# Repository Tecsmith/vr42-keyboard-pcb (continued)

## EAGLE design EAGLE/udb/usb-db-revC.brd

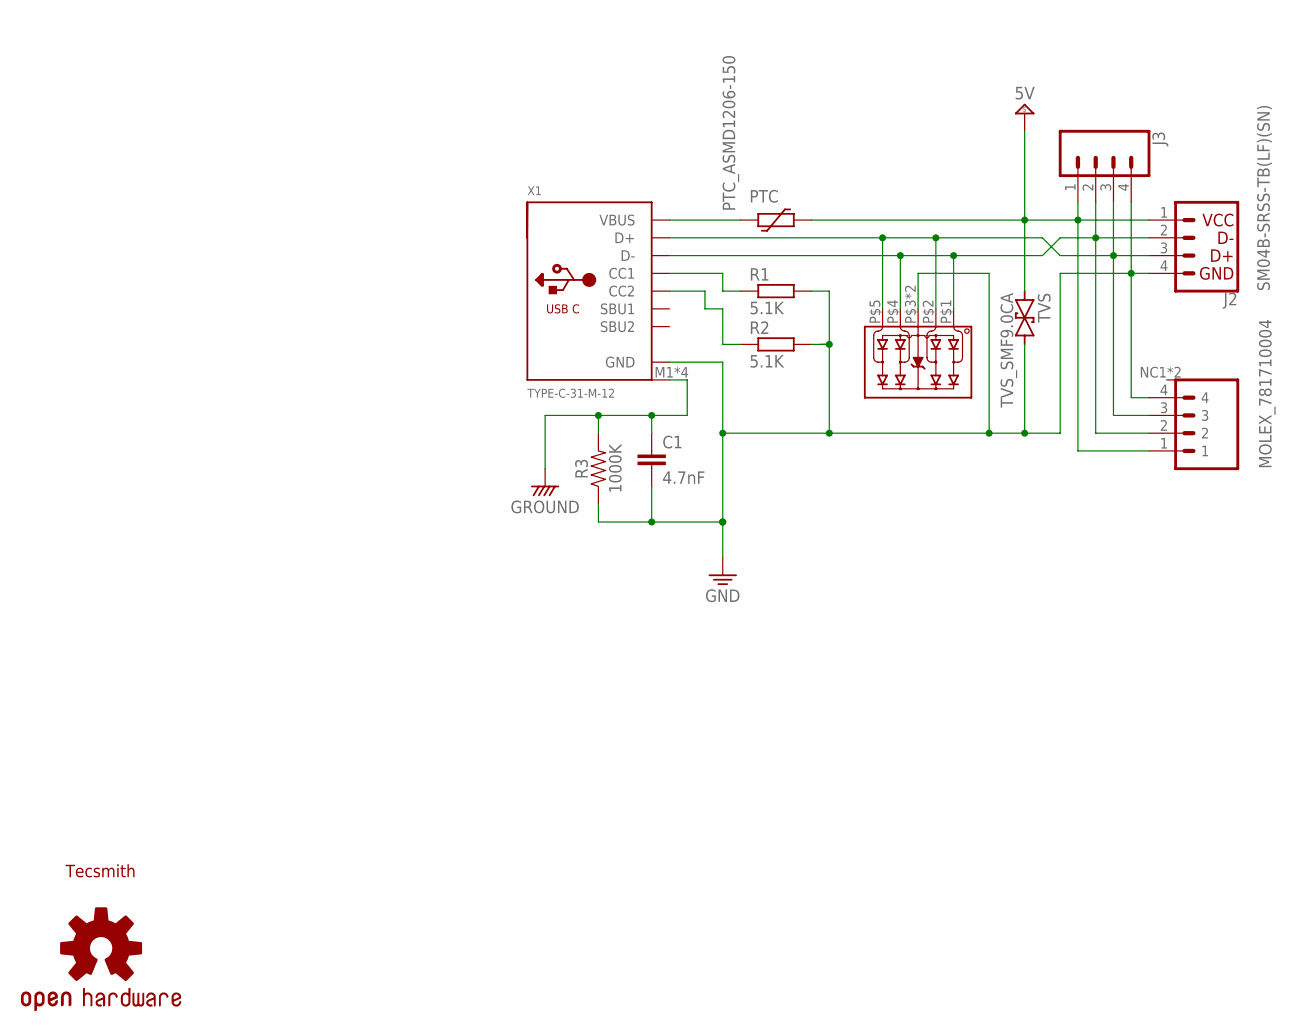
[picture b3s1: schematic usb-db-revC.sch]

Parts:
C1: 4.7nF; 0603
J2: SM04B-SRSS-TB(LF)(SN); 1X04_1MM_RA
J3: CONN_04SMD_RA_FEMALE; 1X04_SMD_RA_FEMALE
LOGO1: OSHW-LOGOS; OSHW-LOGO-S
MOLEX_781710004: MOLEX_0781710004; MOLEX_781710004
PTC: PTC_ASMD1206-150; SMD_PTC
R1, R2: 5.1K; R0402
R3: 1000K; 0603
TVS: TVS_SMF9.0CA; SOD123FL-BI
U$2: TECSMITH-LOGOSHORT; TECSMITH-CUBE
X1: TYPE-C-31-M-12
Y1: ESD_TPD4E05U06; DQA-10-PIN

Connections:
CC1: R1.1, X1.A5-CC1 (CC1)
CC2: R2.1, X1.B5-CC2 (CC2)
D_N: J2.2 (D-), J3.2, MOLEX_781710004.2, X1.A7-DN1 (D-), X1.B7-DN2 (D-), Y1.P$1 (D1+), Y1.P$4 (D2+)
D_P: J2.3 (D+), J3.3, MOLEX_781710004.3, X1.A6-DP1 (D+), X1.B6-DP2 (D+), Y1.P$2 (D1-), Y1.P$5 (D2-)
GND: C1.2, J2.4 (GND), J3.4, MOLEX_781710004.4, R1.2, R2.2, R3.1, TVS.P$2 (2), X1.A1B12-GND (GND), X1.B1A12-GND (GND), Y1.P$3 (GND), Y1.P$8 (GND)
GROUND: C1.1, R3.2, X1.M1 (SHIELD), X1.M2 (SHIELD), X1.M3 (SHIELD), X1.M4 (SHIELD)
VBUS: PTC.P$1 (1), X1.A4B9-VBUS (VBUS), X1.B4A9-VBUS (VBUS)
VSUP: J2.1 (VCC), J3.1, MOLEX_781710004.1, PTC.P$2 (2), TVS.P$1 (1)

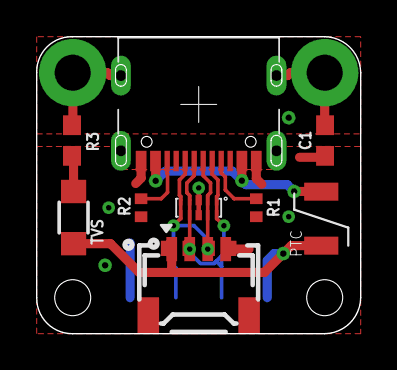
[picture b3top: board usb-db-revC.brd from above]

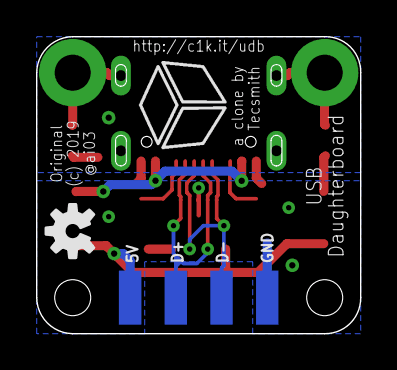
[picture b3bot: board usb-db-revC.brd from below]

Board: 2 copper layers, 18.0 x 16.5 mm, 13 parts (3 on the bottom side), 8 nets.

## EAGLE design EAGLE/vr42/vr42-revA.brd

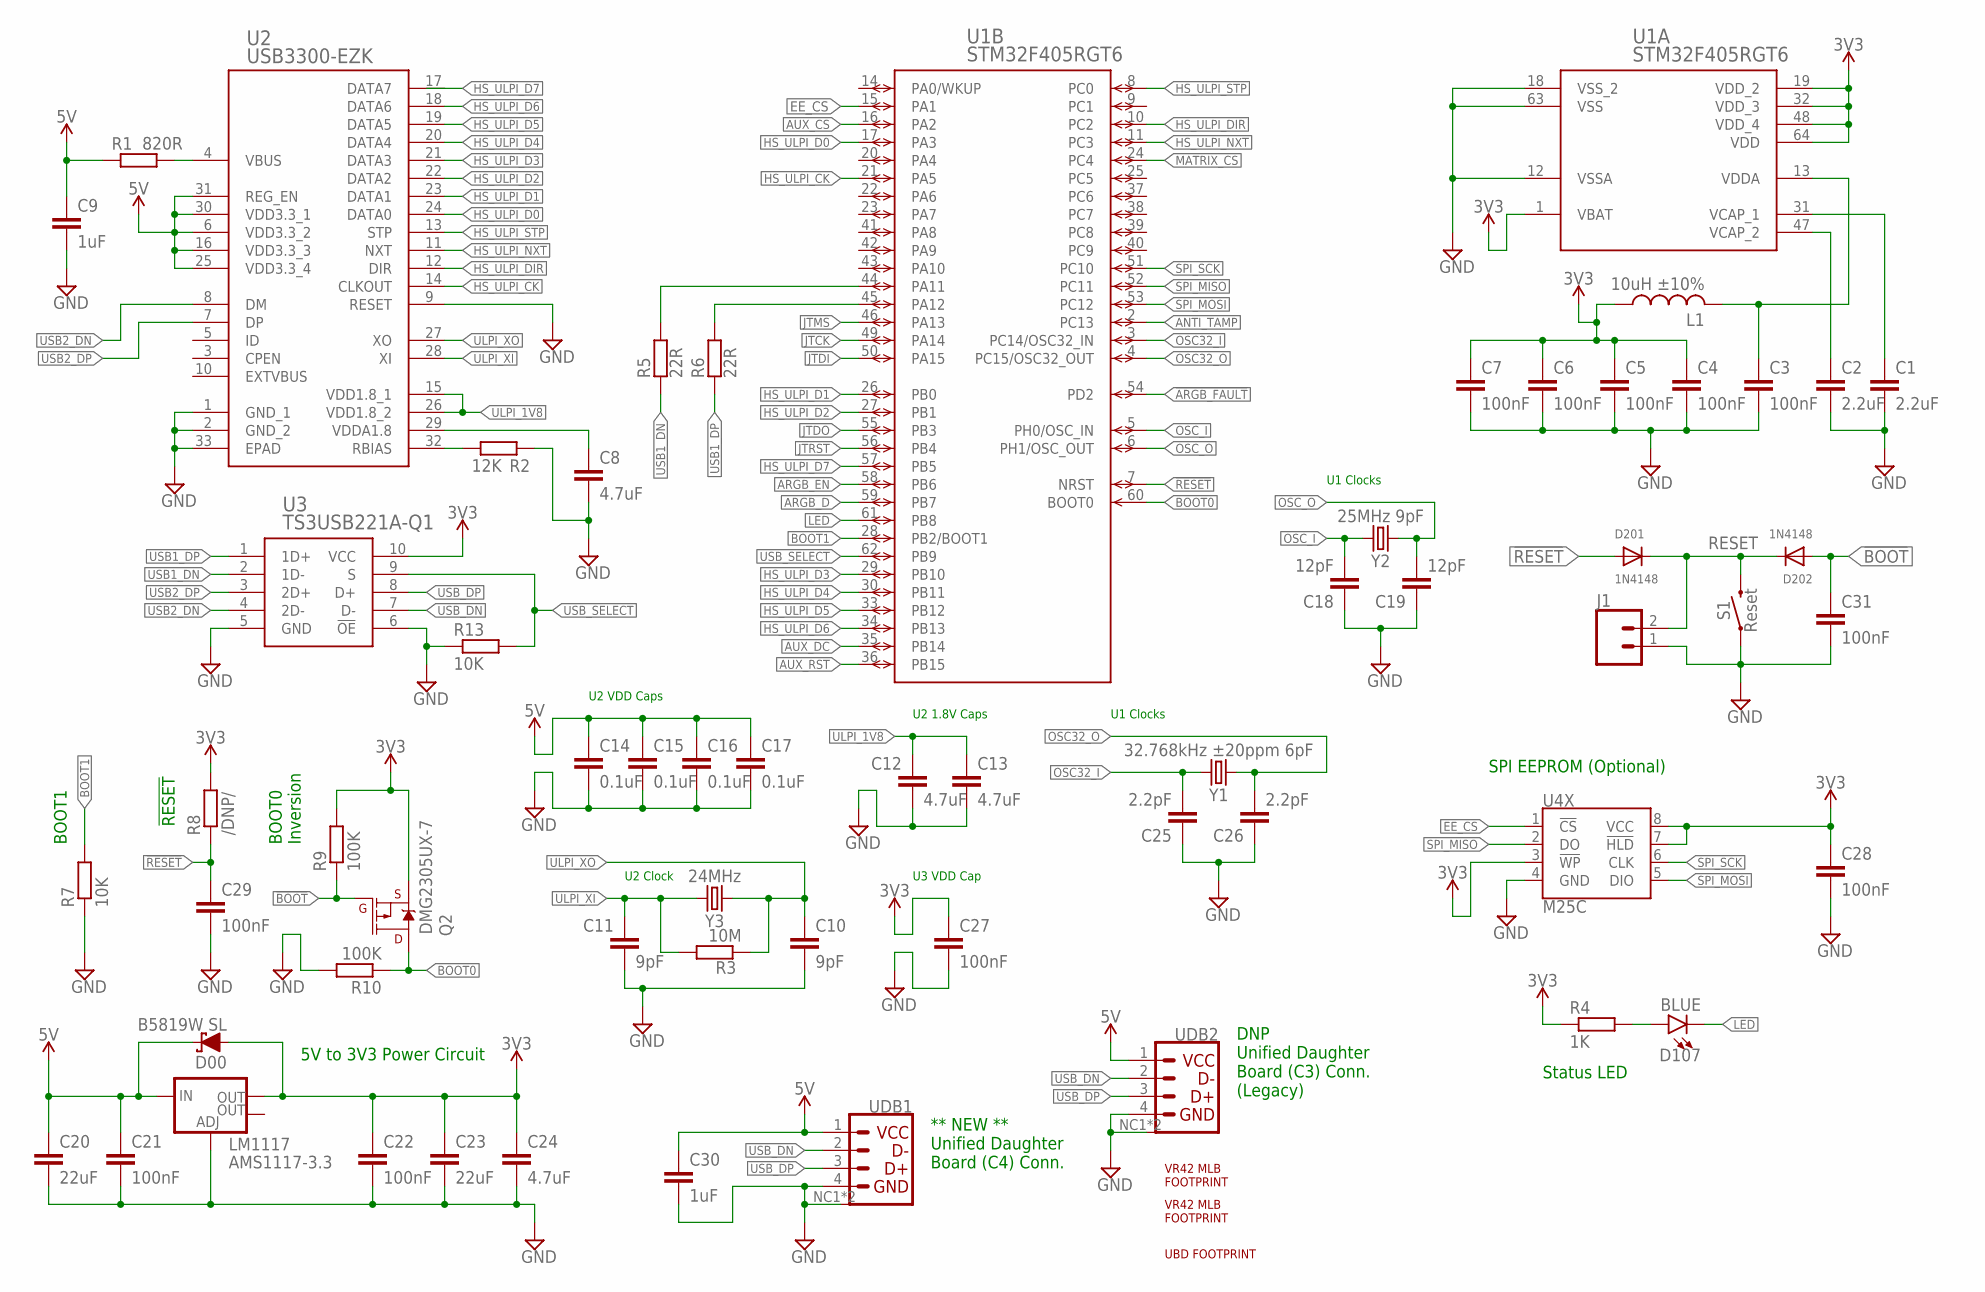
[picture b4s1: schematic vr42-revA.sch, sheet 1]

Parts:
C1, C2: 2.2uF; C0603
C3, C4, C5, C6, C7, C27, C29: 100nF; C0603
C8, C12, C13: 4.7uF; C0603
C9: 1uF; C0603
C10, C11: 9pF; C0603
C14, C15, C16, C17: 0.1uF; C0603
C18, C19: 12pF; C0603
C20, C23: 22uF; 0603
C21, C22, C28: 100nF; 0603
C24: 4.7uF; 0603
C25, C26: 2.2pF; C0603
C30: 1uF; C0805
C31: 100nF; C0805
D00: B5819W SL; SOD-123
D107: BLUE; LED-0603
D201, D202: 1N4148; SOT23-R
J1: CONN_02; 1X02
L1: 10uH ±10%; L3225M
LM1117: AMS1117-3.3; SOT223
Q2: DMG2305UX-7; SOT23-3
R1: 820R; R0603
R2: 12K; R0603
R3: 10M; R0603
R4: 1K; R0603
R5, R6: 22R; R0603
R7, R13: 10K; R0603
R8: /DNP/; R0603
R9, R10: 100K; R0603
S1: Reset; TACTILE_SWITCH_SMD_5.2MM
U1: STM32F405RGT6; LQFP64-10X10MM
U2: USB3300-EZK; QFN32_5X5MC_MCH
U3: TS3USB221A-Q1; RSE10
U4X: M25C; 8-SOIC
U$1, U$6: VR42_MLB_FOOTPRINT
U$7: UBD_FOOTPRINT; UDB_FOOTPRINT
UDB1: UBD-S1_C4; MOLEX_781710004
UDB2: UBD-C3; JST_SM04B-SRSS-TB_LF_SN
Y1: 32.768kHz ±20ppm 6pF; CRYSTAL-SMD-3.2X1.5MM
Y2: 25MHz 9pF; CRYSTAL-SMD-5X3.2-4PAD
Y3: 24MHz; CRYSTAL-SMD-5X3.2-4PAD

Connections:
!ARGB_FAULT: U1.54 (PD2); also elsewhere on the board
!BOOT: C31.1, D202.1 (A), Q2.1 (G), R9.1
!RESET: C29.1, D201.1 (A), R8.1, U1.7 (NRST)
ANTI_TAMP: U1.2 (PC13)
ARGB_D: U1.59 (PB7); also elsewhere on the board
ARGB_EN: U1.58 (PB6); also elsewhere on the board
AUX_CS: U1.16 (PA2); also elsewhere on the board
AUX_DC: U1.35 (PB14); also elsewhere on the board
AUX_RST: U1.36 (PB15); also elsewhere on the board
BOOT0: Q2.3 (D), R10.1, U1.60 (BOOT0)
BOOT1: R7.2, U1.28 (PB2/BOOT1)
EE_CS: U1.15 (PA1), U4X.1 (!CS)
GND: C1.2, C2.2, C3.2, C4.2, C5.2, C6.2, C7.2, C8.2, C9.2, C10.2, C11.2, C12.2, C13.2, C14.2, C15.2, C16.2, C17.2, C18.1, C19.1, C20.2, C21.2, C22.2, C23.2, C24.2, C25.1, C26.1, C27.2, C28.2, C29.2, C30.2, C31.2, J1.1, LM1117.1 (ADJ), R2.2, R7.1, R10.2, R13.1, S1.1, S1.2 (1), U1.12 (VSSA), U1.18 (VSS_2), U1.63 (VSS), U2.1 (GND_1), U2.2 (GND_2), U2.9 (RESET), U2.33 (EPAD), U3.5 (GND), U3.6 (!OE), U4X.4 (GND), UDB1.4 (GND), UDB1.NC1 (M), UDB1.NC2 (M), UDB2.4 (GND), UDB2.NC1 (M), UDB2.NC2 (M); also elsewhere on the board
HS_ULPI_CK: U1.21 (PA5), U2.14 (CLKOUT)
HS_ULPI_D0: U1.17 (PA3), U2.24 (DATA0)
HS_ULPI_D1: U1.26 (PB0), U2.23 (DATA1)
HS_ULPI_D2: U1.27 (PB1), U2.22 (DATA2)
HS_ULPI_D3: U1.29 (PB10), U2.21 (DATA3)
HS_ULPI_D4: U1.30 (PB11), U2.20 (DATA4)
HS_ULPI_D5: U1.33 (PB12), U2.19 (DATA5)
HS_ULPI_D6: U1.34 (PB13), U2.18 (DATA6)
HS_ULPI_D7: U1.57 (PB5), U2.17 (DATA7)
HS_ULPI_DIR: U1.10 (PC2), U2.12 (DIR)
HS_ULPI_NXT: U1.11 (PC3), U2.11 (NXT)
HS_ULPI_STP: U1.8 (PC0), U2.13 (STP)
JTCK: U1.49 (PA14); also elsewhere on the board
JTDI: U1.50 (PA15); also elsewhere on the board
JTDO: U1.55 (PB3); also elsewhere on the board
JTMS: U1.46 (PA13); also elsewhere on the board
JTRST: U1.56 (PB4); also elsewhere on the board
LED: D107.C, U1.61 (PB8)
MATRIX_CS: U1.24 (PC4); also elsewhere on the board
unnamed: R1.2, U2.4 (VBUS)
unnamed: R2.1, U2.32 (RBIAS)
unnamed: C8.1, U2.29 (VDDA1.8)
unnamed: R5.2, U1.44 (PA11)
unnamed: R6.2, U1.45 (PA12)
unnamed: D107.A, R4.2
OSC32_I: C25.2, U1.3 (PC14/OSC32_IN), Y1.P$2 (2)
OSC32_O: C26.2, U1.4 (PC15/OSC32_OUT), Y1.P$1 (1)
OSC_I: C18.2, U1.5 (PH0/OSC_IN), Y2.3 (2)
OSC_O: C19.2, U1.6 (PH1/OSC_OUT), Y2.1
RESET: D201.3 (C), D202.3 (C), J1.2, S1.3 (2), S1.4 (2)
SPI_MISO: U1.52 (PC11), U4X.2 (DO); also elsewhere on the board
SPI_MOSI: U1.53 (PC12), U4X.5 (DIO); also elsewhere on the board
SPI_SCK: U1.51 (PC10), U4X.6 (CLK); also elsewhere on the board
ULPI_1V8: C12.1, C13.1, U2.15 (VDD1.8_1), U2.26 (VDD1.8_2)
ULPI_XI: C11.1, R3.2, U2.28 (XI), Y3.3 (2)
ULPI_XO: C10.1, R3.1, U2.27 (XO), Y3.1
USB1_DN: R5.1, U3.2 (1D-)
USB1_DP: R6.1, U3.1 (1D+)
USB2_DN: U2.8 (DM), U3.4 (2D-)
USB2_DP: U2.7 (DP), U3.3 (2D+)
USB_DN: U3.7 (D-), UDB1.2 (DN), UDB2.2 (DN)
USB_DP: U3.8 (D+), UDB1.3 (DP), UDB2.3 (DP)
USB_SELECT: R13.2, U1.62 (PB9), U3.9 (S)
VCAP_1: C1.1, U1.31 (VCAP_1)
VCAP_2: C2.1, U1.47 (VCAP_2)
VCC_1: C9.1, C14.1, C15.1, C16.1, C17.1, C20.1, C21.1, C30.1, D00.C, LM1117.3 (IN), R1.1, U2.6 (VDD3.3_2), U2.16 (VDD3.3_3), U2.25 (VDD3.3_4), U2.30 (VDD3.3_1), U2.31 (REG_EN), UDB1.1 (VCC), UDB2.1 (VCC); also elsewhere on the board
VCC_2: C4.1, C5.1, C6.1, C7.1, C22.1, C23.1, C24.1, C27.1, C28.1, D00.A, L1.1, LM1117.2 (OUT), Q2.2 (S), R4.1, R8.2, R9.2, U1.1 (VBAT), U1.19 (VDD_2), U1.32 (VDD_3), U1.48 (VDD_4), U1.64 (VDD), U3.10 (VCC), U4X.3 (!WP), U4X.7 (!HLD), U4X.8 (VCC); also elsewhere on the board
VDDA: C3.1, L1.2, U1.13 (VDDA)

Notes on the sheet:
DNP Unified Daughter Board (C3) Conn. (Legacy)
** NEW ** Unified Daughter Board (C4) Conn.
5V to 3V3 Power Circuit
SPI EEPROM (Optional)
BOOT1
BOOT0 Inversion
!RESET
Status LED
U2 VDD Caps
U2 Clock
U3 VDD Cap
U2 1.8V Caps
U1 Clocks

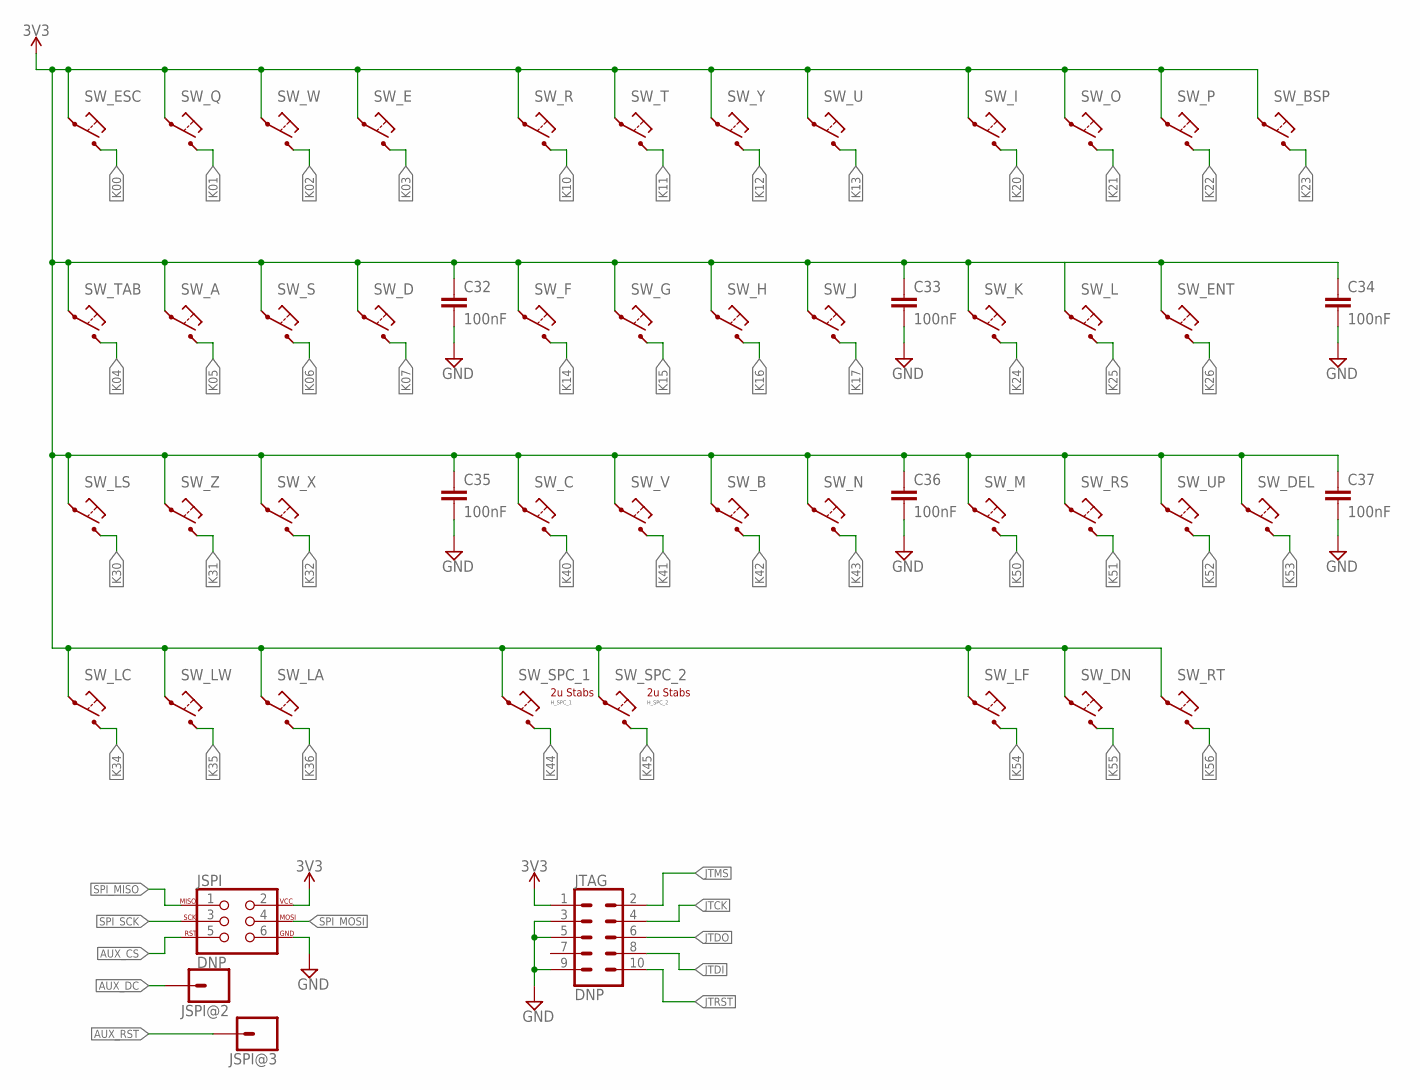
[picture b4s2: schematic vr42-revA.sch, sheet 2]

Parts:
C32, C33, C34, C35, C36, C37: 100nF; C0603
H_SPC_1, H_SPC_2: MX-STABS-200U
JSPI: DNP; 2X3-NS
JSPI@2, JSPI@3: CONN_01; 1X01
JTAG: DNP; 2X5_NOSILK
SW_A: MX-5-PIN-HOTSWAP-PAD
SW_B: MX-5-PIN-HOTSWAP-PAD
SW_BSP: MX-5-PIN-HOTSWAP-PAD
SW_C: MX-5-PIN-HOTSWAP-PAD
SW_D: MX-5-PIN-HOTSWAP-PAD
SW_DEL: MX-5-PIN-HOTSWAP-PAD
SW_DN: MX-5-PIN-HOTSWAP-PAD
SW_E: MX-5-PIN-HOTSWAP-PAD
SW_ENT: MX-5-PIN-HOTSWAP-PAD
SW_ESC: MX-5-PIN-HOTSWAP-PAD
SW_F: MX-5-PIN-HOTSWAP-PAD
SW_G: MX-5-PIN-HOTSWAP-PAD
SW_H: MX-5-PIN-HOTSWAP-PAD
SW_I: MX-5-PIN-HOTSWAP-PAD
SW_J: MX-5-PIN-HOTSWAP-PAD
SW_K: MX-5-PIN-HOTSWAP-PAD
SW_L: MX-5-PIN-HOTSWAP-PAD
SW_LA: MX-5-PIN-HOTSWAP-PAD
SW_LC: MX-5-PIN-HOTSWAP-PAD
SW_LF: MX-5-PIN-HOTSWAP-PAD
SW_LS: MX-5-PIN-HOTSWAP-PAD
SW_LW: MX-5-PIN-HOTSWAP-PAD
SW_M: MX-5-PIN-HOTSWAP-PAD
SW_N: MX-5-PIN-HOTSWAP-PAD
SW_O: MX-5-PIN-HOTSWAP-PAD
SW_P: MX-5-PIN-HOTSWAP-PAD
SW_Q: MX-5-PIN-HOTSWAP-PAD
SW_R: MX-5-PIN-HOTSWAP-PAD
SW_RS: MX-5-PIN-HOTSWAP-PAD
SW_RT: MX-5-PIN-HOTSWAP-PAD
SW_S: MX-5-PIN-HOTSWAP-PAD
SW_SPC_1, SW_SPC_2: MX-5-PIN-HOTSWAP-PAD
SW_T: MX-5-PIN-HOTSWAP-PAD
SW_TAB: MX-5-PIN-HOTSWAP-PAD
SW_U: MX-5-PIN-HOTSWAP-PAD
SW_UP: MX-5-PIN-HOTSWAP-PAD
SW_V: MX-5-PIN-HOTSWAP-PAD
SW_W: MX-5-PIN-HOTSWAP-PAD
SW_X: MX-5-PIN-HOTSWAP-PAD
SW_Y: MX-5-PIN-HOTSWAP-PAD
SW_Z: MX-5-PIN-HOTSWAP-PAD

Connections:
AUX_CS: JSPI.5; also elsewhere on the board
AUX_DC: JSPI@2.1; also elsewhere on the board
AUX_RST: JSPI@3.1; also elsewhere on the board
GND: C32.2, C33.2, C34.2, C35.2, C36.2, C37.2, JSPI.6, JTAG.3, JTAG.5, JTAG.9; also elsewhere on the board
JTCK: JTAG.4; also elsewhere on the board
JTDI: JTAG.8; also elsewhere on the board
JTDO: JTAG.6; also elsewhere on the board
JTMS: JTAG.2; also elsewhere on the board
JTRST: JTAG.10; also elsewhere on the board
K00: SW_ESC.1@1, SW_ESC.1@2; also elsewhere on the board
K01: SW_Q.1@1, SW_Q.1@2; also elsewhere on the board
K02: SW_W.1@1, SW_W.1@2; also elsewhere on the board
K03: SW_E.1@1, SW_E.1@2; also elsewhere on the board
K04: SW_TAB.1@1, SW_TAB.1@2; also elsewhere on the board
K05: SW_A.1@1, SW_A.1@2; also elsewhere on the board
K06: SW_S.1@1, SW_S.1@2; also elsewhere on the board
K07: SW_D.1@1, SW_D.1@2; also elsewhere on the board
K10: SW_R.1@1, SW_R.1@2; also elsewhere on the board
K11: SW_T.1@1, SW_T.1@2; also elsewhere on the board
K12: SW_Y.1@1, SW_Y.1@2; also elsewhere on the board
K13: SW_U.1@1, SW_U.1@2; also elsewhere on the board
K14: SW_F.1@1, SW_F.1@2; also elsewhere on the board
K15: SW_G.1@1, SW_G.1@2; also elsewhere on the board
K16: SW_H.1@1, SW_H.1@2; also elsewhere on the board
K17: SW_J.1@1, SW_J.1@2; also elsewhere on the board
K20: SW_I.1@1, SW_I.1@2; also elsewhere on the board
K21: SW_O.1@1, SW_O.1@2; also elsewhere on the board
K22: SW_P.1@1, SW_P.1@2; also elsewhere on the board
K23: SW_BSP.1@1, SW_BSP.1@2; also elsewhere on the board
K24: SW_K.1@1, SW_K.1@2; also elsewhere on the board
K25: SW_L.1@1, SW_L.1@2; also elsewhere on the board
K26: SW_ENT.1@1, SW_ENT.1@2; also elsewhere on the board
K30: SW_LS.1@1, SW_LS.1@2; also elsewhere on the board
K31: SW_Z.1@1, SW_Z.1@2; also elsewhere on the board
K32: SW_X.1@1, SW_X.1@2; also elsewhere on the board
K34: SW_LC.1@1, SW_LC.1@2; also elsewhere on the board
K35: SW_LW.1@1, SW_LW.1@2; also elsewhere on the board
K36: SW_LA.1@1, SW_LA.1@2; also elsewhere on the board
K40: SW_C.1@1, SW_C.1@2; also elsewhere on the board
K41: SW_V.1@1, SW_V.1@2; also elsewhere on the board
K42: SW_B.1@1, SW_B.1@2; also elsewhere on the board
K43: SW_N.1@1, SW_N.1@2; also elsewhere on the board
K44: SW_SPC_1.1@1, SW_SPC_1.1@2; also elsewhere on the board
K45: SW_SPC_2.1@1, SW_SPC_2.1@2; also elsewhere on the board
K50: SW_M.1@1, SW_M.1@2; also elsewhere on the board
K51: SW_RS.1@1, SW_RS.1@2; also elsewhere on the board
K52: SW_UP.1@1, SW_UP.1@2; also elsewhere on the board
K53: SW_DEL.1@1, SW_DEL.1@2; also elsewhere on the board
K54: SW_LF.1@1, SW_LF.1@2; also elsewhere on the board
K55: SW_DN.1@1, SW_DN.1@2; also elsewhere on the board
K56: SW_RT.1@1, SW_RT.1@2; also elsewhere on the board
SPI_MISO: JSPI.1; also elsewhere on the board
SPI_MOSI: JSPI.4; also elsewhere on the board
SPI_SCK: JSPI.3; also elsewhere on the board
VCC_2: C32.1, C33.1, C34.1, C35.1, C36.1, C37.1, JSPI.2, JTAG.1, SW_A.2@1 (S), SW_A.2@2 (S), SW_B.2@1 (S), SW_B.2@2 (S), SW_BSP.2@1 (S), SW_BSP.2@2 (S), SW_C.2@1 (S), SW_C.2@2 (S), SW_D.2@1 (S), SW_D.2@2 (S), SW_DEL.2@1 (S), SW_DEL.2@2 (S), SW_DN.2@1 (S), SW_DN.2@2 (S), SW_E.2@1 (S), SW_E.2@2 (S), SW_ENT.2@1 (S), SW_ENT.2@2 (S), SW_ESC.2@1 (S), SW_ESC.2@2 (S), SW_F.2@1 (S), SW_F.2@2 (S), SW_G.2@1 (S), SW_G.2@2 (S), SW_H.2@1 (S), SW_H.2@2 (S), SW_I.2@1 (S), SW_I.2@2 (S), SW_J.2@1 (S), SW_J.2@2 (S), SW_K.2@1 (S), SW_K.2@2 (S), SW_L.2@1 (S), SW_L.2@2 (S), SW_LA.2@1 (S), SW_LA.2@2 (S), SW_LC.2@1 (S), SW_LC.2@2 (S), SW_LF.2@1 (S), SW_LF.2@2 (S), SW_LS.2@1 (S), SW_LS.2@2 (S), SW_LW.2@1 (S), SW_LW.2@2 (S), SW_M.2@1 (S), SW_M.2@2 (S), SW_N.2@1 (S), SW_N.2@2 (S), SW_O.2@1 (S), SW_O.2@2 (S), SW_P.2@1 (S), SW_P.2@2 (S), SW_Q.2@1 (S), SW_Q.2@2 (S), SW_R.2@1 (S), SW_R.2@2 (S), SW_RS.2@1 (S), SW_RS.2@2 (S), SW_RT.2@1 (S), SW_RT.2@2 (S), SW_S.2@1 (S), SW_S.2@2 (S), SW_SPC_1.2@1 (S), SW_SPC_1.2@2 (S), SW_SPC_2.2@1 (S), SW_SPC_2.2@2 (S), SW_T.2@1 (S), SW_T.2@2 (S), SW_TAB.2@1 (S), SW_TAB.2@2 (S), SW_U.2@1 (S), SW_U.2@2 (S), SW_UP.2@1 (S), SW_UP.2@2 (S), SW_V.2@1 (S), SW_V.2@2 (S), SW_W.2@1 (S), SW_W.2@2 (S), SW_X.2@1 (S), SW_X.2@2 (S), SW_Y.2@1 (S), SW_Y.2@2 (S), SW_Z.2@1 (S), SW_Z.2@2 (S); also elsewhere on the board

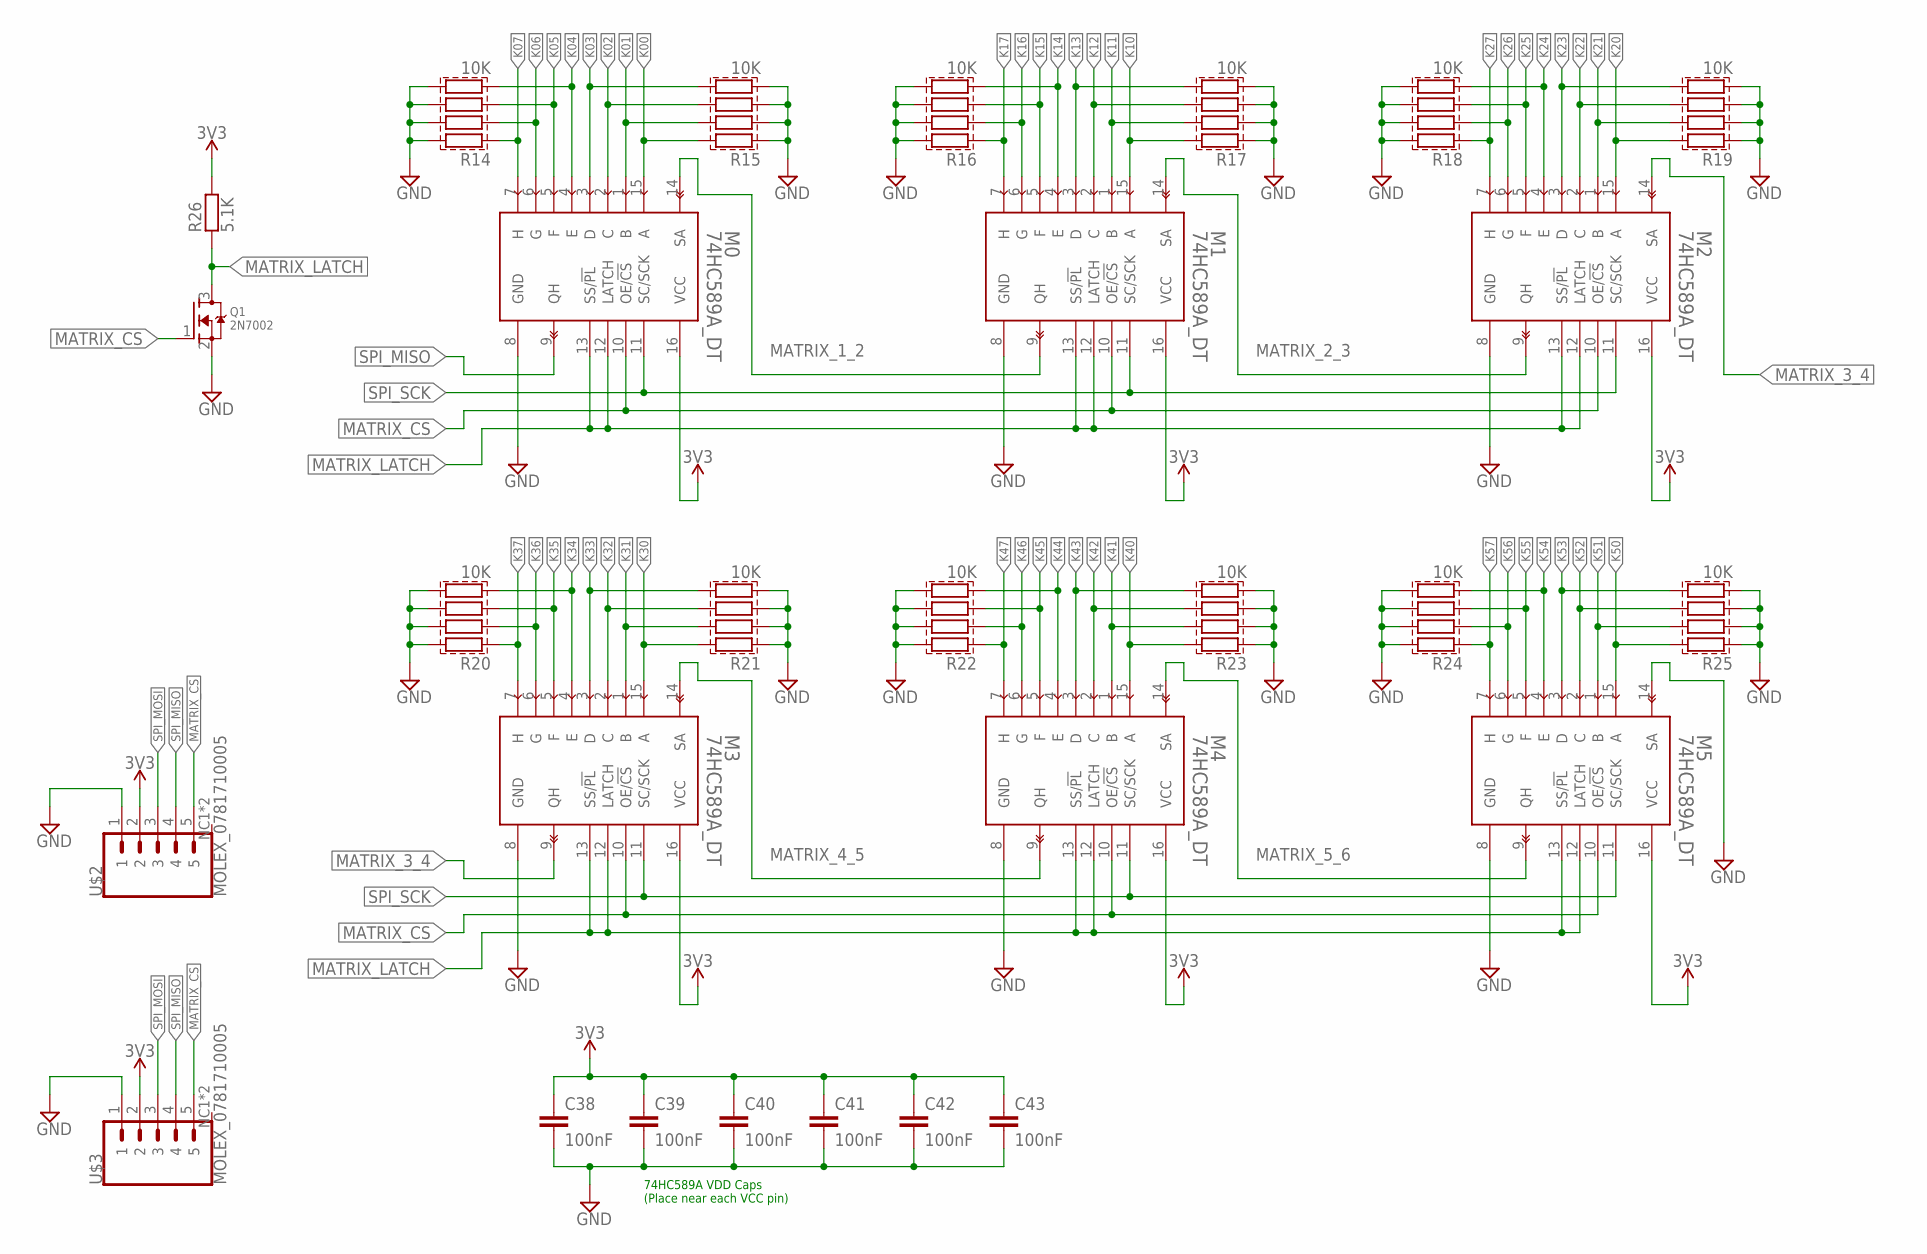
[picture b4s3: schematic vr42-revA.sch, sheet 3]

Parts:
C38, C39, C40, C41, C42, C43: 100nF; 0603
M0, M1, M2, M3, M4, M5: 74HC589A_DT; TSSOP16
Q1: 2N7002; SOT23
R14, R15, R16, R17, R18, R19, R20, R21, R22, R23, R24, R25: 10K; R0603X4
R26: 5.1K; R0603
U$2, U$3: MOLEX_0781710005; MOLEX_781710005

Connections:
GND: C38.2, C39.2, C40.2, C41.2, C42.2, C43.2, M0.8 (GND), M1.8 (GND), M2.8 (GND), M3.8 (GND), M4.8 (GND), M5.8 (GND), M5.14 (SA), Q1.2 (S), R14.5, R14.6, R14.7, R14.8, R15.1, R15.2, R15.3, R15.4, R16.5, R16.6, R16.7, R16.8, R17.1, R17.2, R17.3, R17.4, R18.5, R18.6, R18.7, R18.8, R19.1, R19.2, R19.3, R19.4, R20.5, R20.6, R20.7, R20.8, R21.1, R21.2, R21.3, R21.4, R22.5, R22.6, R22.7, R22.8, R23.1, R23.2, R23.3, R23.4, R24.5, R24.6, R24.7, R24.8, R25.1, R25.2, R25.3, R25.4, U$2.1, U$3.1; also elsewhere on the board
K00: M0.15 (A), R15.8; also elsewhere on the board
K01: M0.1 (B), R15.7; also elsewhere on the board
K02: M0.2 (C), R15.6; also elsewhere on the board
K03: M0.3 (D), R15.5; also elsewhere on the board
K04: M0.4 (E), R14.4; also elsewhere on the board
K05: M0.5 (F), R14.3; also elsewhere on the board
K06: M0.6 (G), R14.2; also elsewhere on the board
K07: M0.7 (H), R14.1; also elsewhere on the board
K10: M1.15 (A), R17.8; also elsewhere on the board
K11: M1.1 (B), R17.7; also elsewhere on the board
K12: M1.2 (C), R17.6; also elsewhere on the board
K13: M1.3 (D), R17.5; also elsewhere on the board
K14: M1.4 (E), R16.4; also elsewhere on the board
K15: M1.5 (F), R16.3; also elsewhere on the board
K16: M1.6 (G), R16.2; also elsewhere on the board
K17: M1.7 (H), R16.1; also elsewhere on the board
K20: M2.15 (A), R19.8; also elsewhere on the board
K21: M2.1 (B), R19.7; also elsewhere on the board
K22: M2.2 (C), R19.6; also elsewhere on the board
K23: M2.3 (D), R19.5; also elsewhere on the board
K24: M2.4 (E), R18.4; also elsewhere on the board
K25: M2.5 (F), R18.3; also elsewhere on the board
K26: M2.6 (G), R18.2; also elsewhere on the board
K27: M2.7 (H), R18.1
K30: M3.15 (A), R21.8; also elsewhere on the board
K31: M3.1 (B), R21.7; also elsewhere on the board
K32: M3.2 (C), R21.6; also elsewhere on the board
K33: M3.3 (D), R21.5
K34: M3.4 (E), R20.4; also elsewhere on the board
K35: M3.5 (F), R20.3; also elsewhere on the board
K36: M3.6 (G), R20.2; also elsewhere on the board
K37: M3.7 (H), R20.1
K40: M4.15 (A), R23.8; also elsewhere on the board
K41: M4.1 (B), R23.7; also elsewhere on the board
K42: M4.2 (C), R23.6; also elsewhere on the board
K43: M4.3 (D), R23.5; also elsewhere on the board
K44: M4.4 (E), R22.4; also elsewhere on the board
K45: M4.5 (F), R22.3; also elsewhere on the board
K46: M4.6 (G), R22.2
K47: M4.7 (H), R22.1
K50: M5.15 (A), R25.8; also elsewhere on the board
K51: M5.1 (B), R25.7; also elsewhere on the board
K52: M5.2 (C), R25.6; also elsewhere on the board
K53: M5.3 (D), R25.5; also elsewhere on the board
K54: M5.4 (E), R24.4; also elsewhere on the board
K55: M5.5 (F), R24.3; also elsewhere on the board
K56: M5.6 (G), R24.2; also elsewhere on the board
K57: M5.7 (H), R24.1
MATRIX_1_2: M0.14 (SA), M1.9 (QH)
MATRIX_2_3: M1.14 (SA), M2.9 (QH)
MATRIX_3_4: M2.14 (SA), M3.9 (QH)
MATRIX_4_5: M3.14 (SA), M4.9 (QH)
MATRIX_5_6: M4.14 (SA), M5.9 (QH)
MATRIX_CS: M0.10 (OE/!CS), M1.10 (OE/!CS), M2.10 (OE/!CS), M3.10 (OE/!CS), M4.10 (OE/!CS), M5.10 (OE/!CS), Q1.1 (G), U$2.5, U$3.5; also elsewhere on the board
MATRIX_LATCH: M0.12 (LATCH), M0.13 (SS/!PL), M1.12 (LATCH), M1.13 (SS/!PL), M2.12 (LATCH), M2.13 (SS/!PL), M3.12 (LATCH), M3.13 (SS/!PL), M4.12 (LATCH), M4.13 (SS/!PL), M5.12 (LATCH), M5.13 (SS/!PL), Q1.3 (D), R26.1
SPI_MISO: M0.9 (QH), U$2.4, U$3.4; also elsewhere on the board
SPI_MOSI: U$2.3, U$3.3; also elsewhere on the board
SPI_SCK: M0.11 (SC/SCK), M1.11 (SC/SCK), M2.11 (SC/SCK), M3.11 (SC/SCK), M4.11 (SC/SCK), M5.11 (SC/SCK); also elsewhere on the board
VCC_2: C38.1, C39.1, C40.1, C41.1, C42.1, C43.1, M0.16 (VCC), M1.16 (VCC), M2.16 (VCC), M3.16 (VCC), M4.16 (VCC), M5.16 (VCC), R26.2, U$2.2, U$3.2; also elsewhere on the board

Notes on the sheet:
74HC589A VDD Caps (Place near each VCC pin)

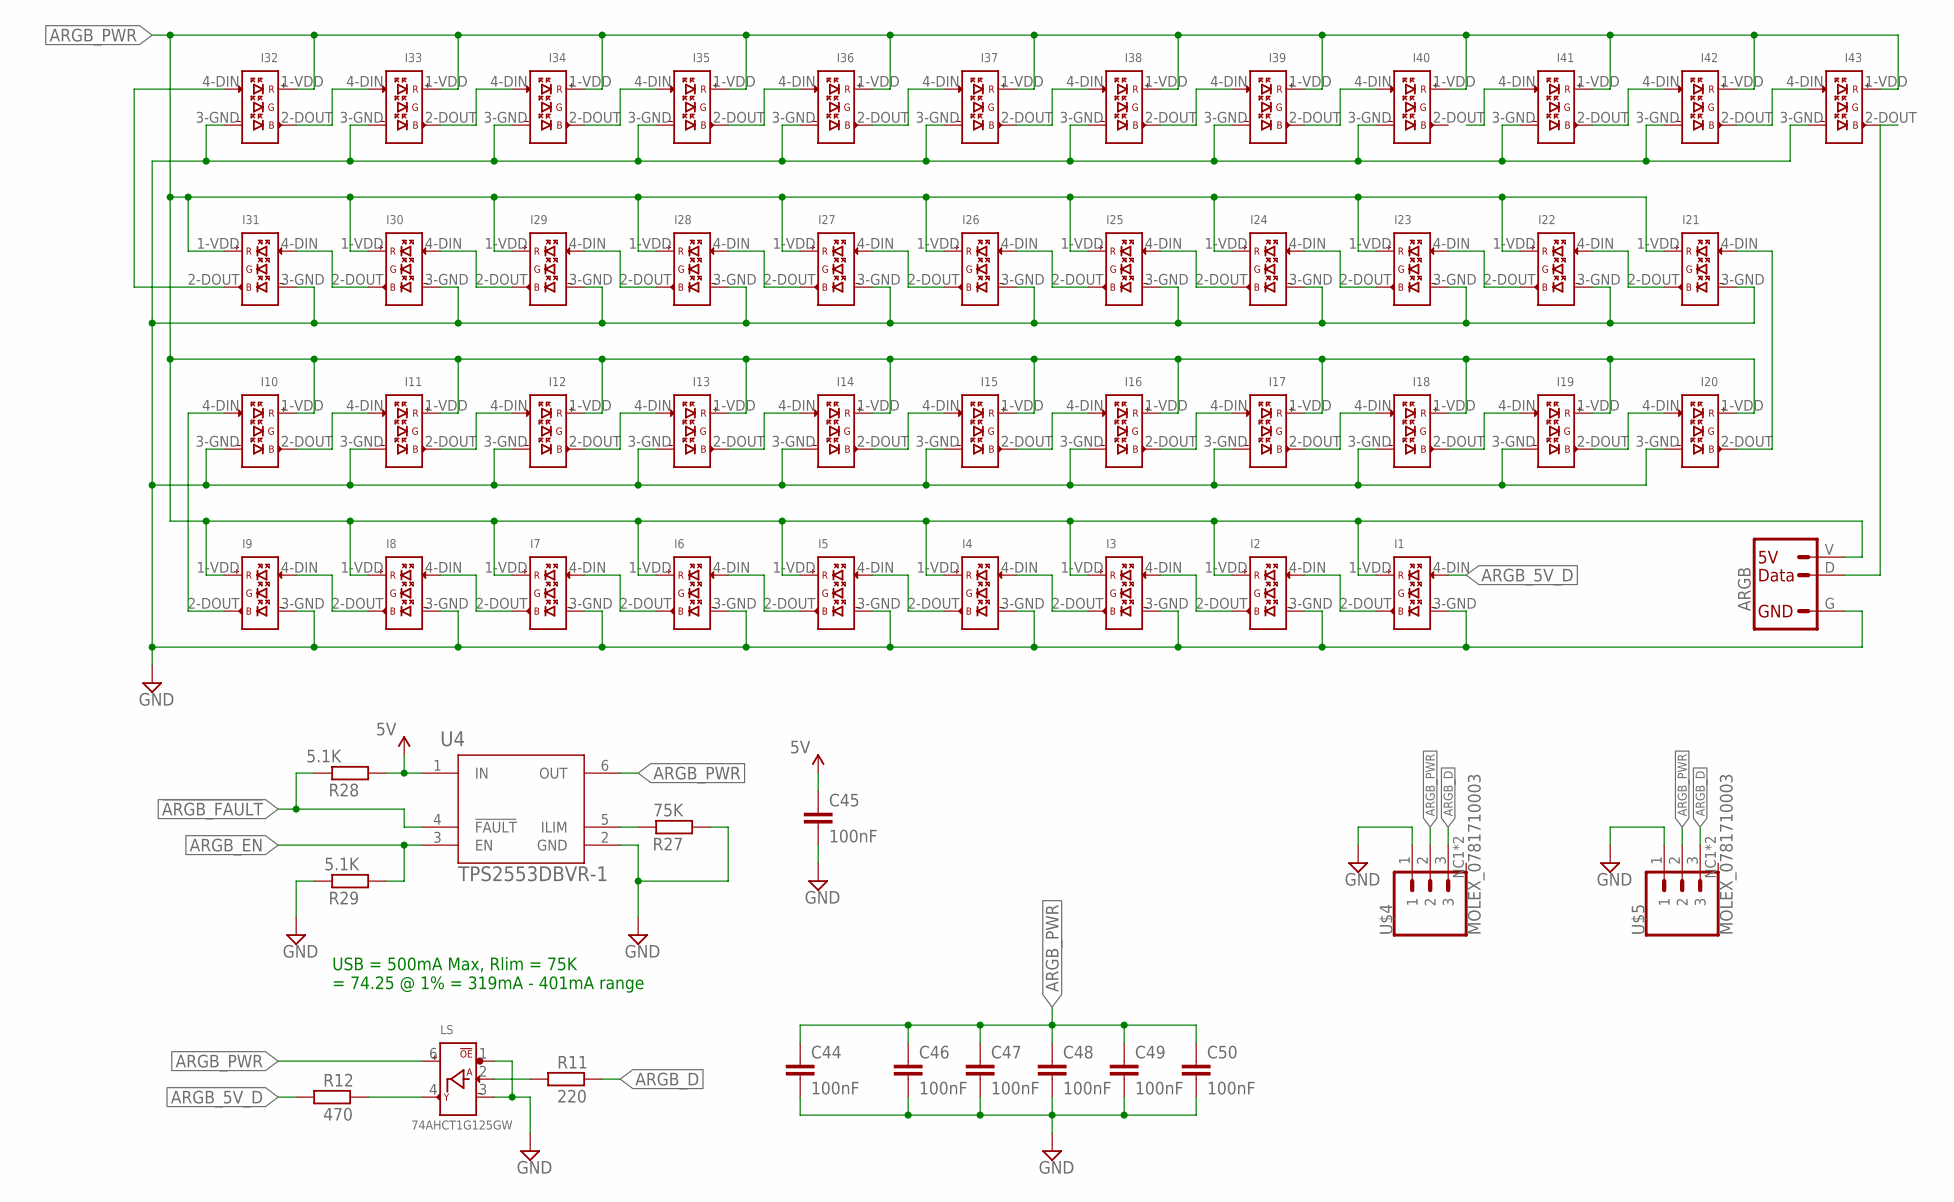
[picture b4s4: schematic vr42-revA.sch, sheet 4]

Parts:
C44, C45, C46, C47, C48, C49, C50: 100nF; C0603
I1, I2, I3, I4, I5, I6, I7, I8, I9, I10, I11, I12, I13, I14, I15, I16, I17, I18, I19, I20, I21, I22, I23, I24, I25, I26, I27, I28, I29, I30, I31, I32, I33, I34, I35, I36, I37, I38, I39, I40, I41, I42, I43: SK6812-E-REVERSE; SK6812-E-MILL
I44: ARGB
LS: 74AHCT1G125GW; SC-88A__TSSOP5__SOT353-1
R11: 220; R0603
R12: 470; R0603
R27: 75K; R0603
R28, R29: 5.1K; R0603
U4: TPS2553DBVR-1; DBV0006A_N
U$4, U$5: MOLEX_0781710003; MOLEX_781710003

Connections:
!ARGB_FAULT: R28.2, U4.4 (!FAULT); also elsewhere on the board
ARGB_5V_D: I1.4-DIN (4_DIN), R12.1
ARGB_D: R11.2, U$4.3, U$5.3; also elsewhere on the board
ARGB_EN: R29.1, U4.3 (EN); also elsewhere on the board
ARGB_PWR: C44.1, C46.1, C47.1, C48.1, C49.1, C50.1, I1.1-VDD (1_VDD), I2.1-VDD (1_VDD), I3.1-VDD (1_VDD), I4.1-VDD (1_VDD), I5.1-VDD (1_VDD), I6.1-VDD (1_VDD), I7.1-VDD (1_VDD), I8.1-VDD (1_VDD), I9.1-VDD (1_VDD), I10.1-VDD (1_VDD), I11.1-VDD (1_VDD), I12.1-VDD (1_VDD), I13.1-VDD (1_VDD), I14.1-VDD (1_VDD), I15.1-VDD (1_VDD), I16.1-VDD (1_VDD), I17.1-VDD (1_VDD), I18.1-VDD (1_VDD), I19.1-VDD (1_VDD), I20.1-VDD (1_VDD), I21.1-VDD (1_VDD), I22.1-VDD (1_VDD), I23.1-VDD (1_VDD), I24.1-VDD (1_VDD), I25.1-VDD (1_VDD), I26.1-VDD (1_VDD), I27.1-VDD (1_VDD), I28.1-VDD (1_VDD), I29.1-VDD (1_VDD), I30.1-VDD (1_VDD), I31.1-VDD (1_VDD), I32.1-VDD (1_VDD), I33.1-VDD (1_VDD), I34.1-VDD (1_VDD), I35.1-VDD (1_VDD), I36.1-VDD (1_VDD), I37.1-VDD (1_VDD), I38.1-VDD (1_VDD), I39.1-VDD (1_VDD), I40.1-VDD (1_VDD), I41.1-VDD (1_VDD), I42.1-VDD (1_VDD), I43.1-VDD (1_VDD), I44.V, LS.6 (5_VCC), U4.6 (OUT), U$4.2, U$5.2
GND: C44.2, C45.2, C46.2, C47.2, C48.2, C49.2, C50.2, I1.3-GND (3_GND), I2.3-GND (3_GND), I3.3-GND (3_GND), I4.3-GND (3_GND), I5.3-GND (3_GND), I6.3-GND (3_GND), I7.3-GND (3_GND), I8.3-GND (3_GND), I9.3-GND (3_GND), I10.3-GND (3_GND), I11.3-GND (3_GND), I12.3-GND (3_GND), I13.3-GND (3_GND), I14.3-GND (3_GND), I15.3-GND (3_GND), I16.3-GND (3_GND), I17.3-GND (3_GND), I18.3-GND (3_GND), I19.3-GND (3_GND), I20.3-GND (3_GND), I21.3-GND (3_GND), I22.3-GND (3_GND), I23.3-GND (3_GND), I24.3-GND (3_GND), I25.3-GND (3_GND), I26.3-GND (3_GND), I27.3-GND (3_GND), I28.3-GND (3_GND), I29.3-GND (3_GND), I30.3-GND (3_GND), I31.3-GND (3_GND), I32.3-GND (3_GND), I33.3-GND (3_GND), I34.3-GND (3_GND), I35.3-GND (3_GND), I36.3-GND (3_GND), I37.3-GND (3_GND), I38.3-GND (3_GND), I39.3-GND (3_GND), I40.3-GND (3_GND), I41.3-GND (3_GND), I42.3-GND (3_GND), I43.3-GND (3_GND), I44.G, LS.1 (!OE), LS.3 (3_GND), R27.1, R29.2, U4.2 (GND), U$4.1, U$5.1; also elsewhere on the board
LED1ST: LS.2 (A_DIN), R11.1
unnamed: I9.2-DOUT (2_DOUT), I10.4-DIN (4_DIN)
unnamed: I32.2-DOUT (2_DOUT), I33.4-DIN (4_DIN)
unnamed: I33.2-DOUT (2_DOUT), I34.4-DIN (4_DIN)
unnamed: I34.2-DOUT (2_DOUT), I35.4-DIN (4_DIN)
unnamed: I35.2-DOUT (2_DOUT), I36.4-DIN (4_DIN)
unnamed: I36.2-DOUT (2_DOUT), I37.4-DIN (4_DIN)
unnamed: I37.2-DOUT (2_DOUT), I38.4-DIN (4_DIN)
unnamed: I38.2-DOUT (2_DOUT), I39.4-DIN (4_DIN)
unnamed: I39.2-DOUT (2_DOUT), I40.4-DIN (4_DIN)
unnamed: I23.2-DOUT (2_DOUT), I24.4-DIN (4_DIN)
unnamed: I24.2-DOUT (2_DOUT), I25.4-DIN (4_DIN)
unnamed: I25.2-DOUT (2_DOUT), I26.4-DIN (4_DIN)
unnamed: I26.2-DOUT (2_DOUT), I27.4-DIN (4_DIN)
unnamed: I27.2-DOUT (2_DOUT), I28.4-DIN (4_DIN)
unnamed: I29.2-DOUT (2_DOUT), I30.4-DIN (4_DIN)
unnamed: I30.2-DOUT (2_DOUT), I31.4-DIN (4_DIN)
unnamed: I20.2-DOUT (2_DOUT), I21.4-DIN (4_DIN)
unnamed: I10.2-DOUT (2_DOUT), I11.4-DIN (4_DIN)
unnamed: I11.2-DOUT (2_DOUT), I12.4-DIN (4_DIN)
unnamed: I12.2-DOUT (2_DOUT), I13.4-DIN (4_DIN)
unnamed: I13.2-DOUT (2_DOUT), I14.4-DIN (4_DIN)
unnamed: I14.2-DOUT (2_DOUT), I15.4-DIN (4_DIN)
unnamed: I15.2-DOUT (2_DOUT), I16.4-DIN (4_DIN)
unnamed: I16.2-DOUT (2_DOUT), I17.4-DIN (4_DIN)
unnamed: I5.2-DOUT (2_DOUT), I6.4-DIN (4_DIN)
unnamed: I6.2-DOUT (2_DOUT), I7.4-DIN (4_DIN)
unnamed: I7.2-DOUT (2_DOUT), I8.4-DIN (4_DIN)
unnamed: I8.2-DOUT (2_DOUT), I9.4-DIN (4_DIN)
unnamed: I31.2-DOUT (2_DOUT), I32.4-DIN (4_DIN)
unnamed: I43.2-DOUT (2_DOUT), I44.D
unnamed: R27.2, U4.5 (ILIM)
unnamed: I19.2-DOUT (2_DOUT), I20.4-DIN (4_DIN)
unnamed: I41.2-DOUT (2_DOUT), I42.4-DIN (4_DIN)
unnamed: I28.2-DOUT (2_DOUT), I29.4-DIN (4_DIN)
unnamed: I1.2-DOUT (2_DOUT), I2.4-DIN (4_DIN)
unnamed: I42.2-DOUT (2_DOUT), I43.4-DIN (4_DIN)
unnamed: I21.2-DOUT (2_DOUT), I22.4-DIN (4_DIN)
unnamed: I22.2-DOUT (2_DOUT), I23.4-DIN (4_DIN)
unnamed: I2.2-DOUT (2_DOUT), I3.4-DIN (4_DIN)
unnamed: I3.2-DOUT (2_DOUT), I4.4-DIN (4_DIN)
unnamed: I4.2-DOUT (2_DOUT), I5.4-DIN (4_DIN)
unnamed: I17.2-DOUT (2_DOUT), I18.4-DIN (4_DIN)
unnamed: I18.2-DOUT (2_DOUT), I19.4-DIN (4_DIN)
unnamed: LS.4 (Y_DOUT), R12.2
VCC_1: C45.1, R28.1, U4.1 (IN); also elsewhere on the board

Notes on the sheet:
USB = 500mA Max, Rlim = 75K = 74.25 @ 1% = 319mA - 401mA range
